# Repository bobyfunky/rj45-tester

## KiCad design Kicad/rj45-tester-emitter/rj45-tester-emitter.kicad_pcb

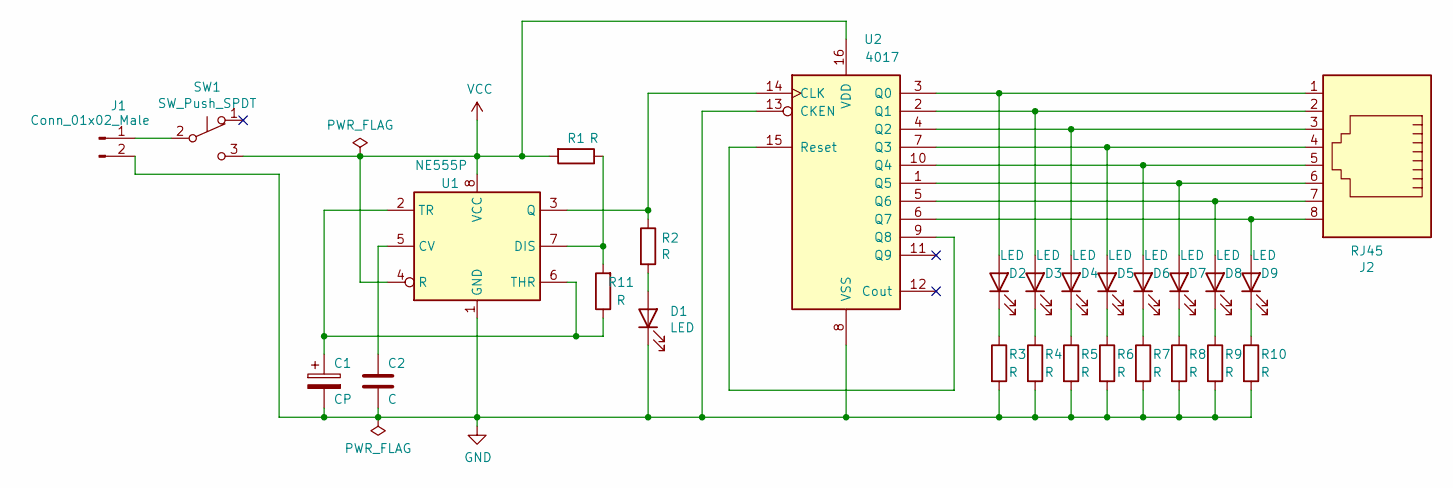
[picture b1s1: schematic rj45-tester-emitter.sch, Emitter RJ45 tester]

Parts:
C1: CP; CP_Elec_6.3x5.2
C2: C; C_0805_2012Metric_Pad1.15x1.40mm_HandSolder
D1, D2, D3, D4, D5, D6, D7, D8, D9: LED; LED_0805_2012Metric_Pad1.15x1.40mm_HandSolder
J1: Conn_01x02_Male; JST_XH_B2B-XH-A_1x02_P2.50mm_Vertical
J2: RJ45
R1, R2, R3, R4, R5, R6, R7, R8, R9, R10, R11: R; R_0805_2012Metric_Pad1.15x1.40mm_HandSolder
SW1: SW_Push_SPDT
U1: NE555P; DIP-8_W8.89mm_SMDSocket_LongPads
U2: 4017; DIP-16_W8.89mm_SMDSocket_LongPads

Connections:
GND: C1.2, C2.2, D1.1 (K), J1.2, R3.2, R4.2, R5.2, R6.2, R7.2, R8.2, R9.2, R10.2, U1.1 (GND), U2.8 (VSS), U2.13 (CKEN)
unnamed: C1.1, R11.1, U1.2 (TR), U1.6 (THR)
unnamed: C2.1, U1.5 (CV)
unnamed: D1.2 (A), R2.2
unnamed: D2.1 (K), R3.1
unnamed: D2.2 (A), J2.1, U2.3 (Q0)
unnamed: D3.1 (K), R4.1
unnamed: D3.2 (A), J2.2, U2.2 (Q1)
unnamed: D4.1 (K), R5.1
unnamed: D4.2 (A), J2.3, U2.4 (Q2)
unnamed: D5.1 (K), R6.1
unnamed: D5.2 (A), J2.4, U2.7 (Q3)
unnamed: D6.1 (K), R7.1
unnamed: D6.2 (A), J2.5, U2.10 (Q4)
unnamed: D7.1 (K), R8.1
unnamed: D7.2 (A), J2.6, U2.1 (Q5)
unnamed: D8.1 (K), R9.1
unnamed: D8.2 (A), J2.7, U2.5 (Q6)
unnamed: D9.1 (K), R10.1
unnamed: D9.2 (A), J2.8, U2.6 (Q7)
unnamed: J1.1, SW1.2 (B)
unnamed: R1.1, R11.2, U1.7 (DIS)
unnamed: R2.1, U1.3 (Q), U2.14 (CLK)
unnamed: U2.9 (Q8), U2.15 (Reset)
VCC: R1.2, SW1.3 (C), U1.4 (R), U1.8 (VCC), U2.16 (VDD)

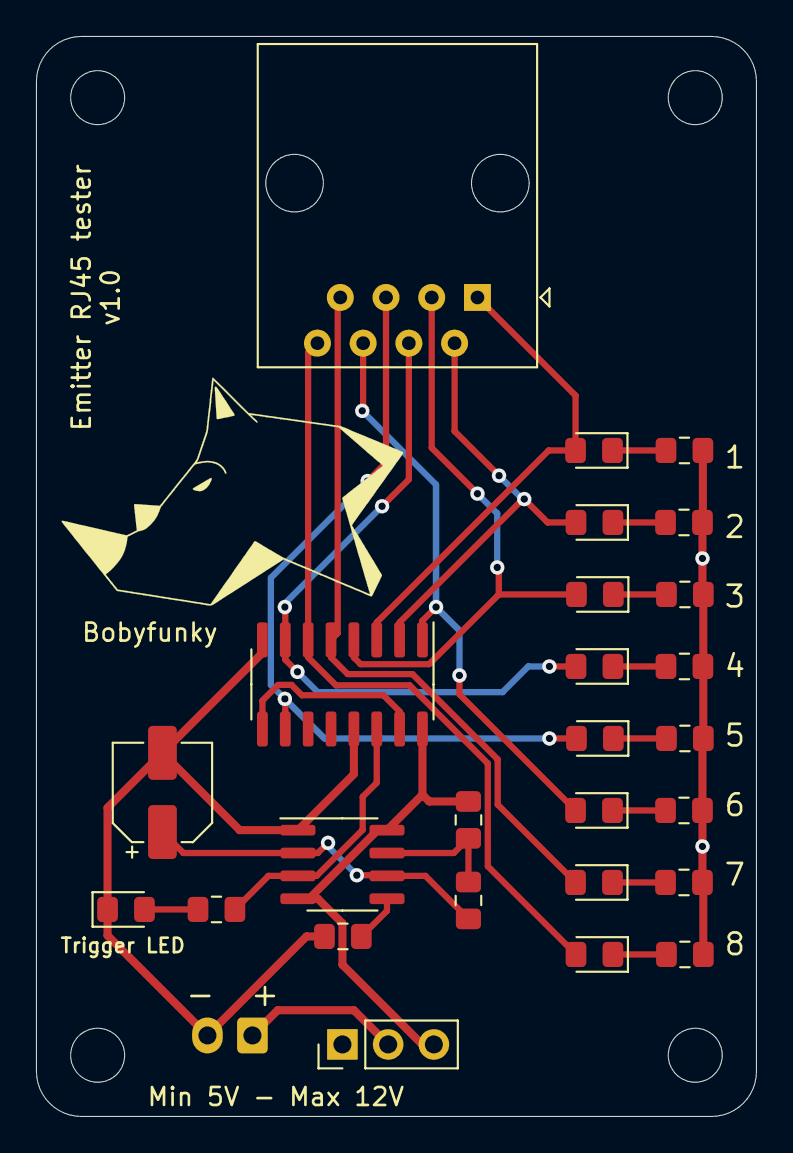
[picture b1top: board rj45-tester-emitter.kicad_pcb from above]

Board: 2 copper layers, 40.0 x 60.0 mm, 27 parts (1 on the bottom side), 25 nets.

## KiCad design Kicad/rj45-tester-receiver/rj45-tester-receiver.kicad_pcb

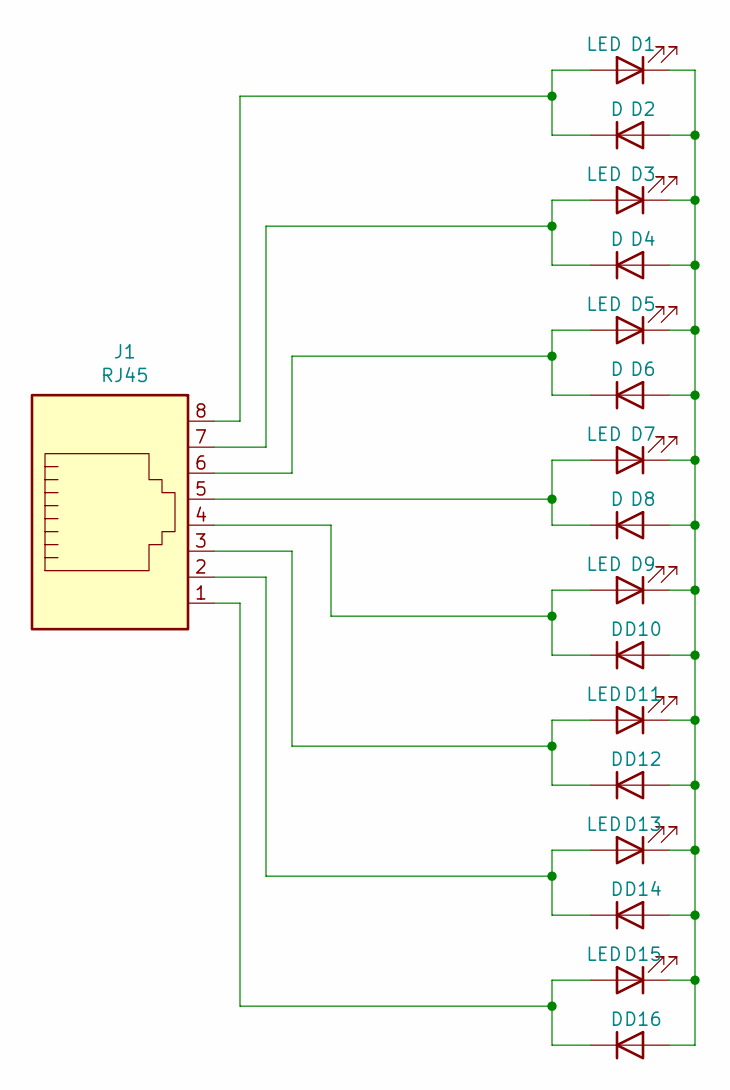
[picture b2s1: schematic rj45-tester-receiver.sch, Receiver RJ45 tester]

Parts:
D1, D3, D5, D7, D9, D11, D13, D15: LED; LED_0805_2012Metric_Pad1.15x1.40mm_HandSolder
D2, D4, D6, D8, D10, D12, D14, D16: D; D_0805_2012Metric_Pad1.15x1.40mm_HandSolder
J1: RJ45; RJ45_Amphenol_54602-x08_Horizontal

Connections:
unnamed: D1.1 (K), D2.2 (A), D3.1 (K), D4.2 (A), D5.1 (K), D6.2 (A), D7.1 (K), D8.2 (A), D9.1 (K), D10.2 (A), D11.1 (K), D12.2 (A), D13.1 (K), D14.2 (A), D15.1 (K), D16.2 (A)
unnamed: D1.2 (A), D2.1 (K), J1.8
unnamed: D3.2 (A), D4.1 (K), J1.7
unnamed: D5.2 (A), D6.1 (K), J1.6
unnamed: D7.2 (A), D8.1 (K), J1.5
unnamed: D9.2 (A), D10.1 (K), J1.4
unnamed: D11.2 (A), D12.1 (K), J1.3
unnamed: D13.2 (A), D14.1 (K), J1.2
unnamed: D15.2 (A), D16.1 (K), J1.1

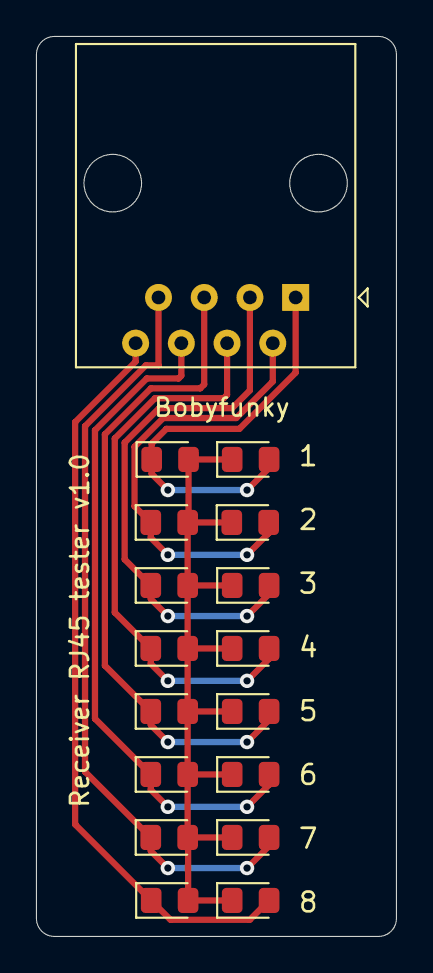
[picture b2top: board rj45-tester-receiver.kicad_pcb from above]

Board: 2 copper layers, 20.0 x 50.0 mm, 17 parts (0 on the bottom side), 9 nets.

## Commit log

2020-09-10 Init repo
2020-09-13 Add switch + bypass capacitor
2020-09-14 PCB finished
2020-09-14 PCB receiver
2020-09-21 Drill Holes
2020-10-18 Add components values
